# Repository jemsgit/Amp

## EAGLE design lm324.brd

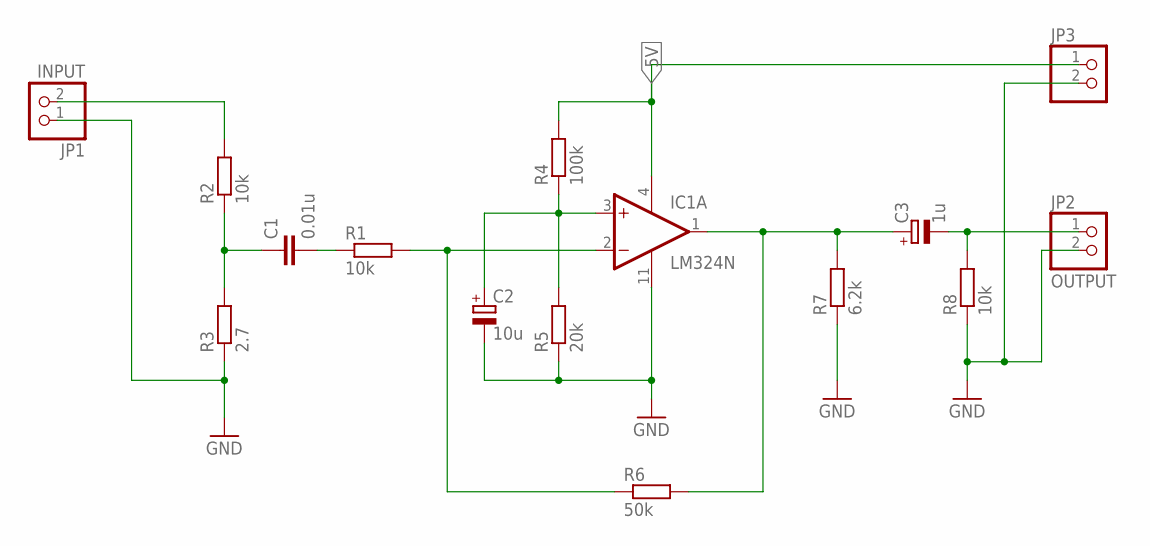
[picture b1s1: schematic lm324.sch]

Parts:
C1: 0.01u; C0805
C2: 10u; E3,5-8
C3: 1u; E3,5-8
IC1: LM324N; DIL14
JP1: INPUT; 1X02
JP2: OUTPUT; 1X02
JP3: PINHD-1X2; 1X02
R1, R2, R8: 10k; R0805
R3: 2.7; R0805
R4: 100k; R0805
R5: 20k; R0805
R6: 50k; R0805
R7: 6.2k; R0805

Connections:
5V: IC1.4 (V+), JP3.1, R4.2
GND: C2.-, IC1.11 (V-), JP1.1, JP2.2, JP3.2, R3.1, R5.1, R7.1, R8.1
unnamed: IC1.2 (-IN), R1.2, R6.1
unnamed: C1.1, R2.1, R3.2
unnamed: JP1.2, R2.2
unnamed: C1.2, R1.1
unnamed: C2.+, IC1.3 (+IN), R4.1, R5.2
unnamed: C3.+, IC1.1 (OUT), R6.2, R7.2
unnamed: C3.-, JP2.1, R8.2

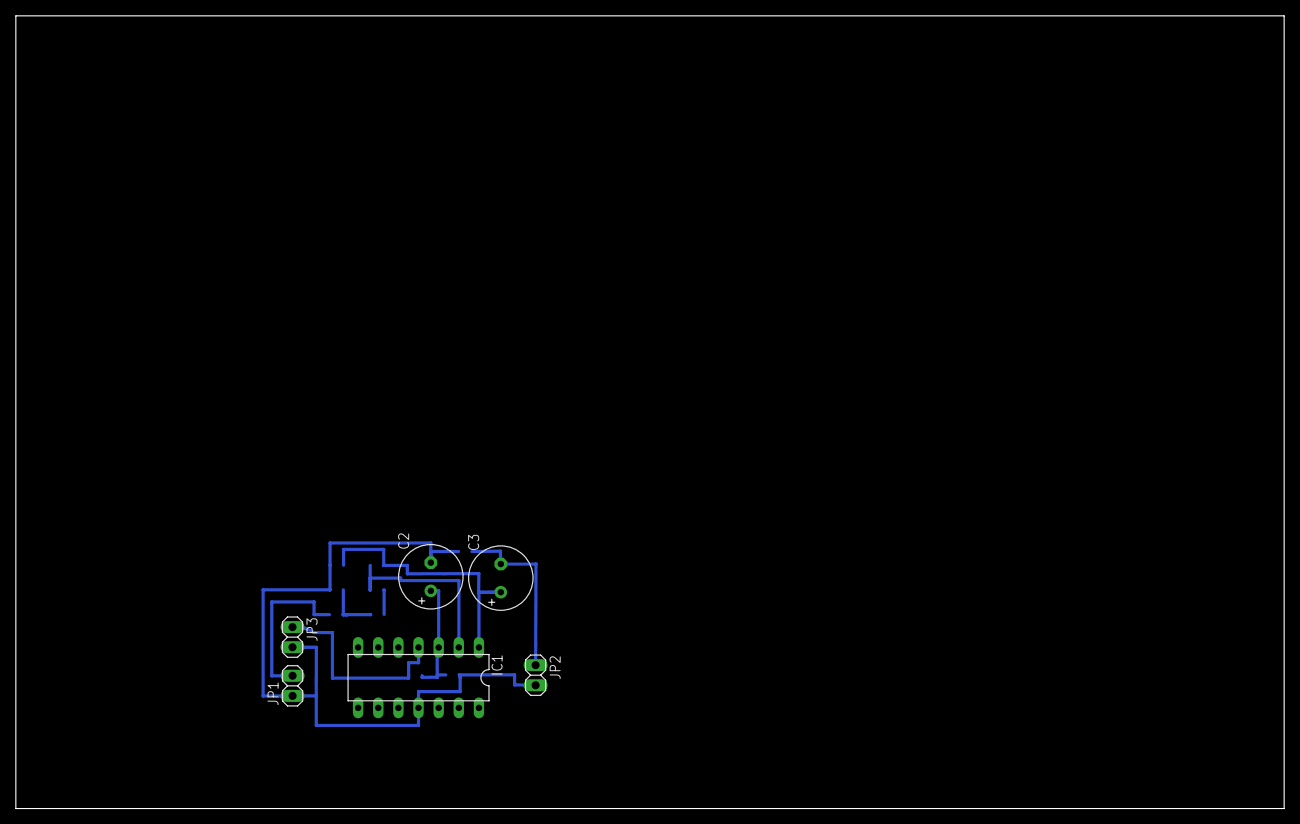
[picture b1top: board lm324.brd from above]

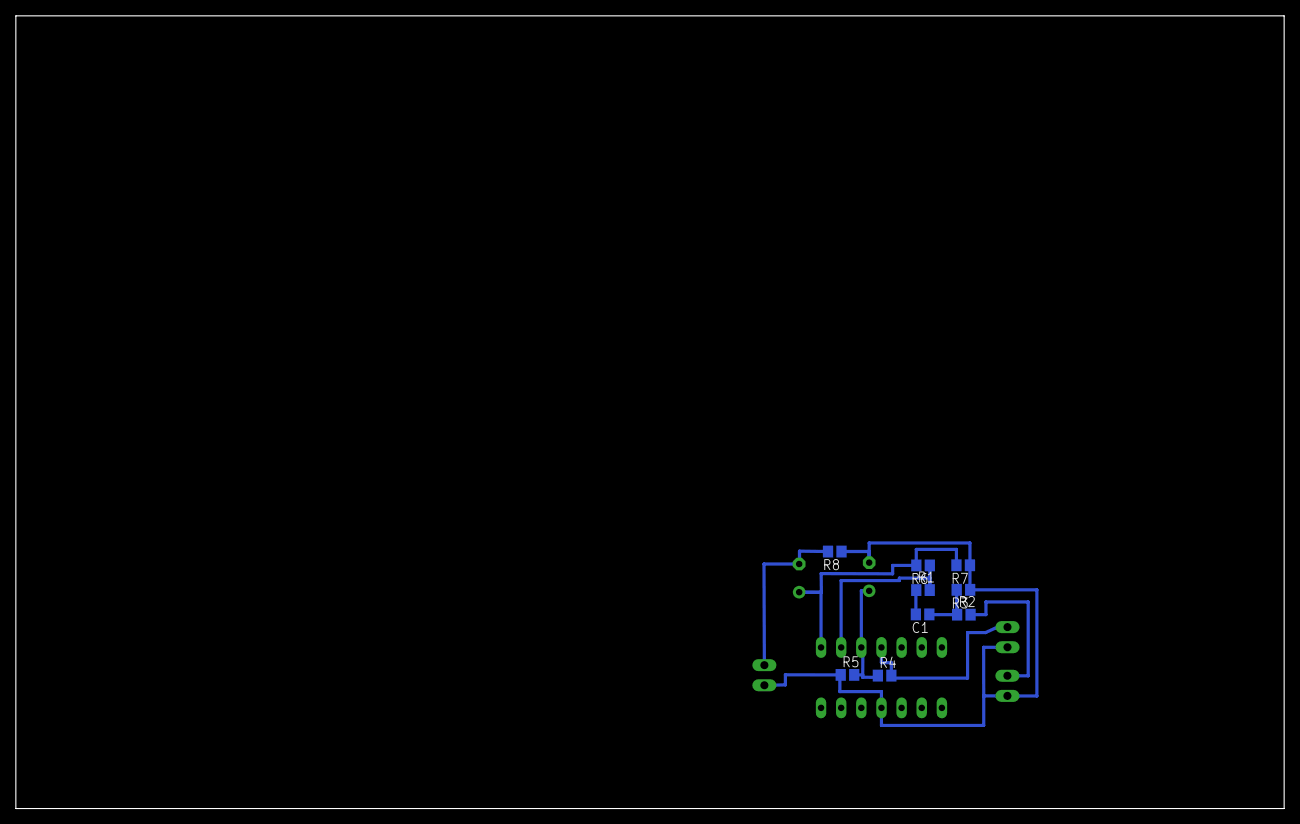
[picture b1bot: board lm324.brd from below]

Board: 2 copper layers, 160.0 x 100.0 mm, 15 parts (9 on the bottom side), 9 nets.

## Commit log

2014-07-02 Sch and Brd
2014-07-03 BRD2
2014-07-03 BRD3
2014-07-07 Rate R6 & R5
